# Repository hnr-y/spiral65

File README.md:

# Keyboard
 A simple 65 WKL keyboard.

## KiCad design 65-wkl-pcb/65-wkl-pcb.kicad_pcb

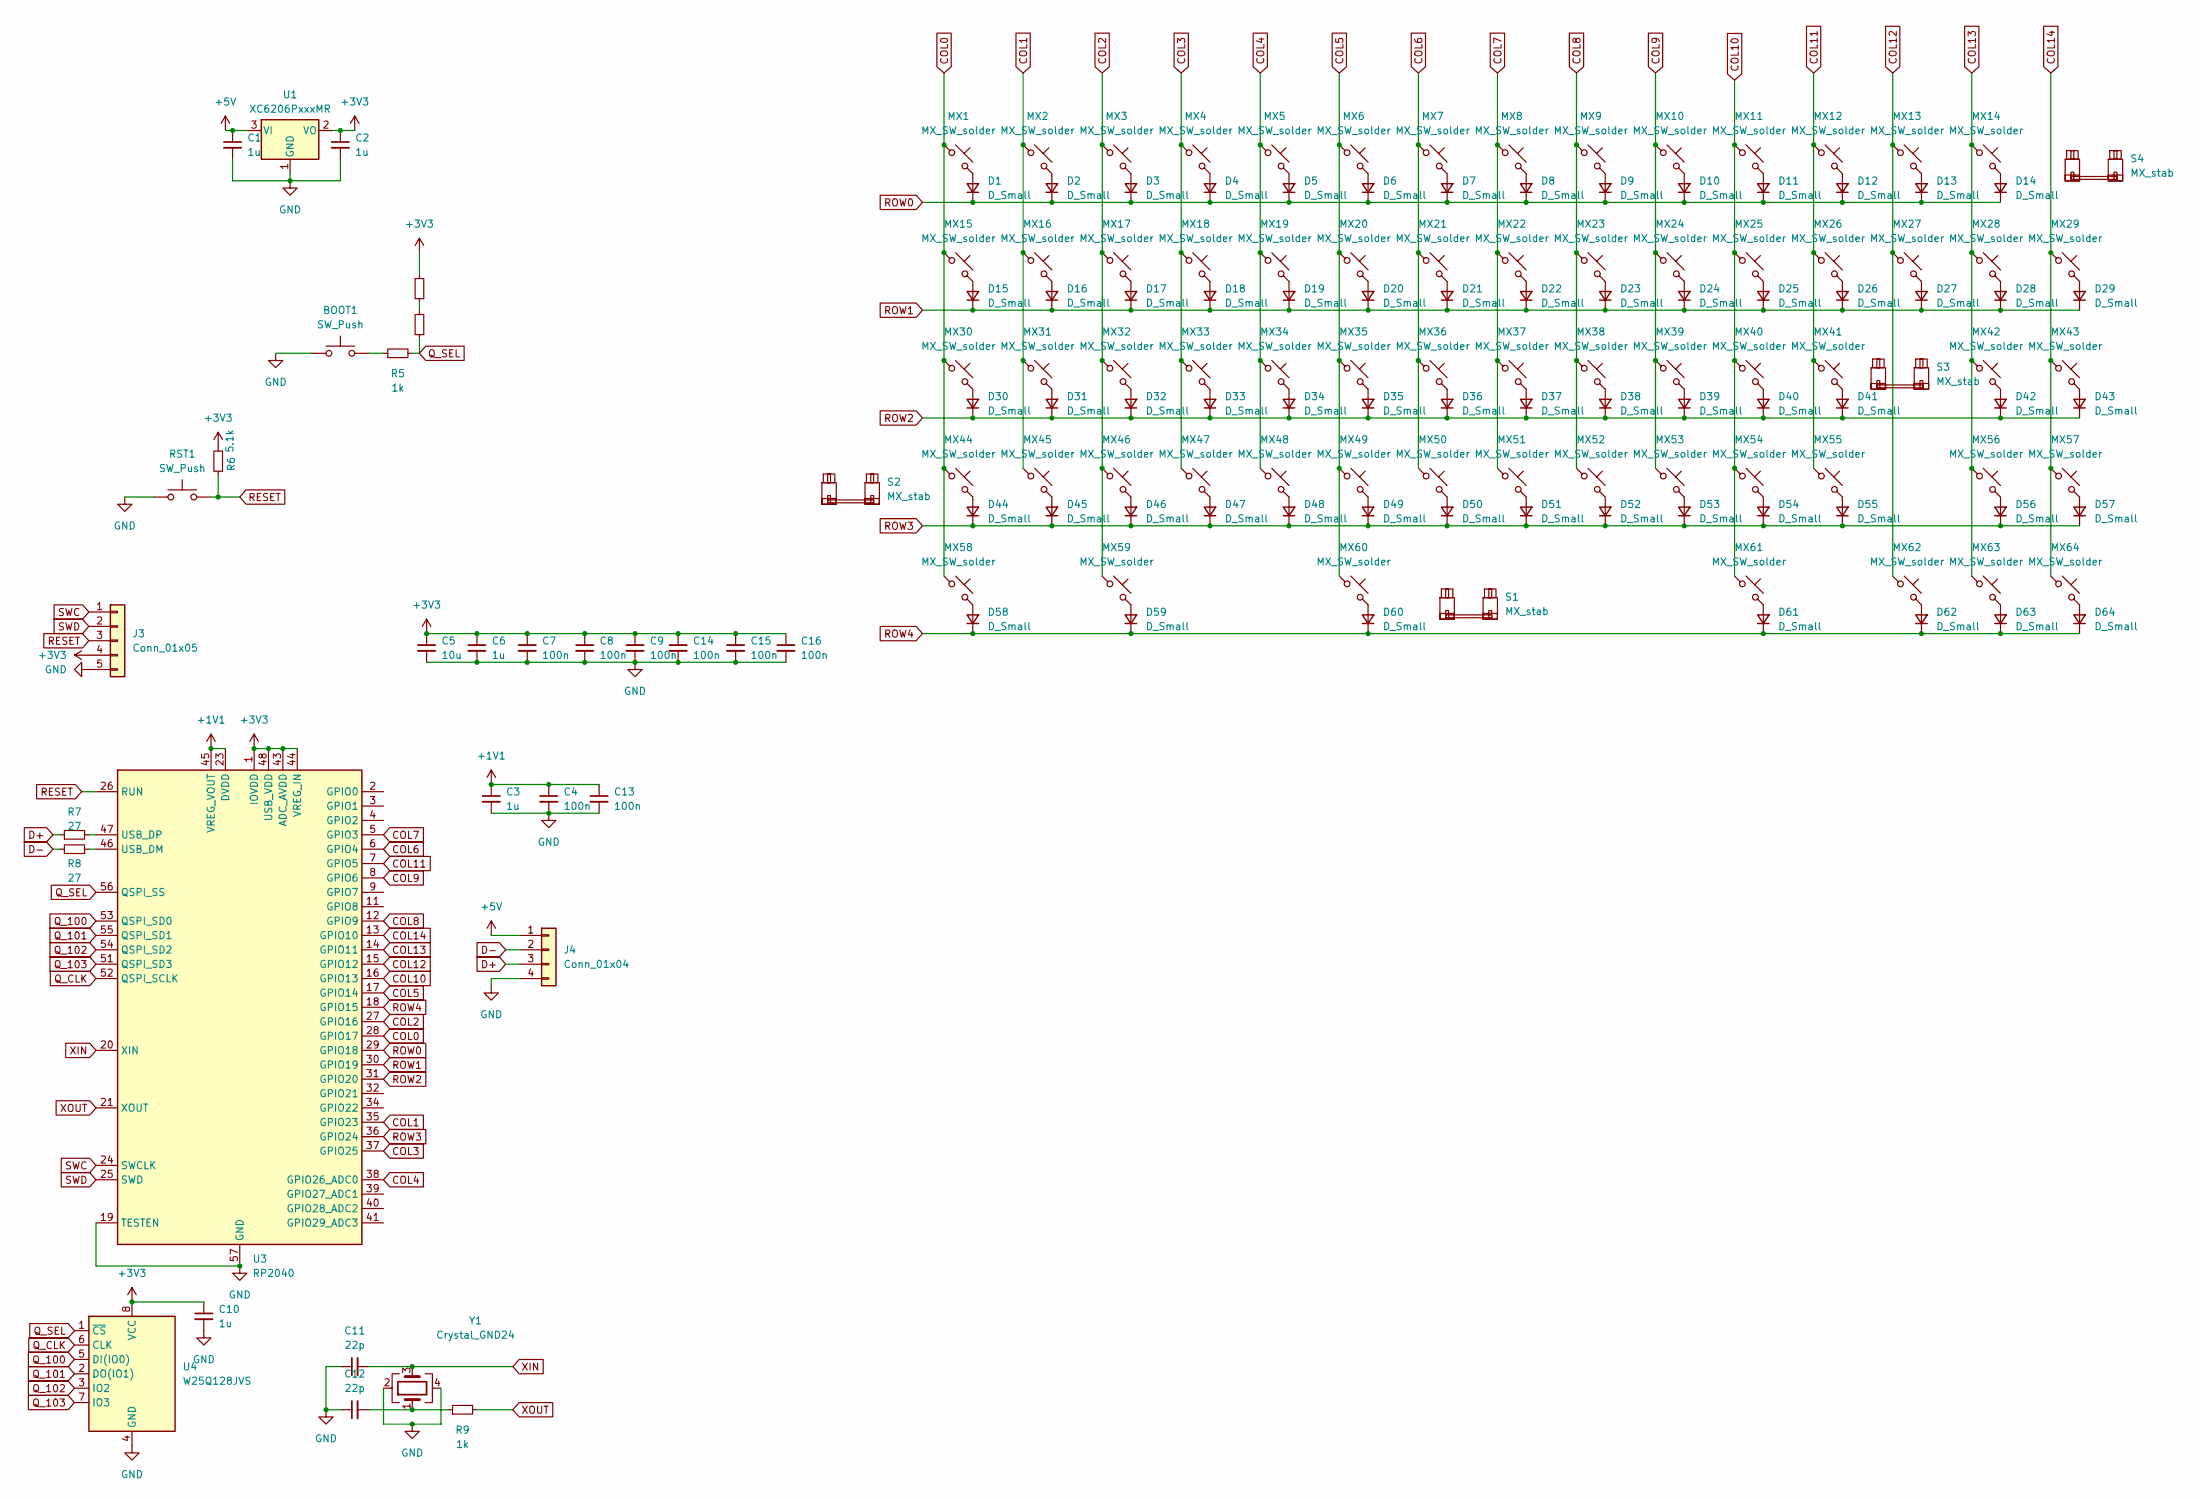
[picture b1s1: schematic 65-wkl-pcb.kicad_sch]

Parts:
BOOT1: SW_Push; SW_SPST_TL3342
C1, C2, C3, C6, C10: 1u; C_0402_1005Metric
C4, C7, C8, C9, C13, C14, C15, C16: 100n; C_0402_1005Metric
C5: 10u; C_0603_1608Metric
C11, C12: 22p; C_0402_1005Metric
D1, D2, D3, D4, D5, D6, D7, D8, D9, D10, D11, D12, D13, D14, D15, D16, D17, D18, D19, D20, D21, D22, D23, D24, D25, D26, D27, D28, D29, D30, D31, D32, D33, D34, D35, D36, D37, D38, D39, D40, D41, D42, D43, D44, D45, D46, D47, D48, D49, D50, D51, D52, D53, D54, D55, D56, D57, D58, D59, D60, D61, D62, D63, D64: D_Small; D_SOD-123
J3: Conn_01x05; PinHeader_1x05_P2.54mm_Vertical
J4: Conn_01x04; Molex_Pico-EZmate_78171-0004_1x04-1MP_P1.20mm_Vertical
MX1, MX2, MX3, MX4, MX5, MX6, MX7, MX8, MX9, MX10, MX11, MX12, MX13, MX14, MX16, MX17, MX18, MX19, MX20, MX21, MX22, MX23, MX24, MX25, MX26, MX27, MX28, MX29, MX31, MX32, MX33, MX34, MX35, MX36, MX37, MX38, MX39, MX40, MX41, MX42, MX43, MX44, MX45, MX46, MX47, MX48, MX49, MX50, MX51, MX52, MX53, MX54, MX56, MX57, MX60, MX61, MX62, MX63, MX64: MX_SW_solder; SW_MX_1u
MX15, MX58, MX59: MX_SW_solder; SW_MX_1.5u
MX30, MX55: MX_SW_solder; SW_MX_1.75u
R3, R4, R6: 5.1k; R_0402_1005Metric
R5, R9: 1k; R_0402_1005Metric
R7, R8: 27; R_0402_1005Metric
RST1: SW_Push; SW_SPST_TL3342
S1: MX_stab; STAB_MX_P_7u
S2, S3: MX_stab; STAB_MX_P_2.25u
S4: MX_stab; STAB_MX_P_2u
U1: XC6206PxxxMR; SOT-23-3
U3: RP2040; QFN-56-1EP_7x7mm_P0.4mm_EP3.2x3.2mm
U4: W25Q128JVS; SOIC-8_5.23x5.23mm_P1.27mm
Y1: Crystal_GND24; Crystal_SMD_3225-4Pin_3.2x2.5mm

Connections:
+1V1: C3.1, C4.1, C13.1, U3.23 (DVDD), U3.45 (VREG_VOUT), U3.50 (DVDD)
+3V3: C2.1, C5.1, C6.1, C7.1, C8.1, C9.1, C10.1, C14.1, C15.1, C16.1, J3.4, R3.2, R6.2, U1.2 (VO), U3.1 (IOVDD), U3.10 (IOVDD), U3.22 (IOVDD), U3.33 (IOVDD), U3.42 (IOVDD), U3.43 (ADC_AVDD), U3.44 (VREG_IN), U3.48 (USB_VDD), U3.49 (IOVDD), U4.8 (VCC)
+5V: C1.1, J4.1, U1.3 (VI)
COL0: MX1.1, MX15.1, MX30.1, MX44.1, MX58.1, U3.28 (GPIO17)
COL1: MX2.1, MX16.1, MX31.1, MX45.1, U3.35 (GPIO23)
COL2: MX3.1, MX17.1, MX32.1, MX46.1, MX59.1, U3.27 (GPIO16)
COL3: MX4.1, MX18.1, MX33.1, MX47.1, U3.37 (GPIO25)
COL4: MX5.1, MX19.1, MX34.1, MX48.1, U3.38 (GPIO26_ADC0)
COL5: MX6.1, MX20.1, MX35.1, MX49.1, MX60.1, U3.17 (GPIO14)
COL6: MX7.1, MX21.1, MX36.1, MX50.1, U3.6 (GPIO4)
COL7: MX8.1, MX22.1, MX37.1, MX51.1, U3.5 (GPIO3)
COL8: MX9.1, MX23.1, MX38.1, MX52.1, U3.12 (GPIO9)
COL9: MX10.1, MX24.1, MX39.1, MX53.1, U3.8 (GPIO6)
COL10: MX11.1, MX25.1, MX40.1, MX54.1, MX61.1, U3.16 (GPIO13)
COL11: MX12.1, MX26.1, MX41.1, MX55.1, U3.7 (GPIO5)
COL12: MX13.1, MX27.1, MX62.1, U3.15 (GPIO12)
COL13: MX14.1, MX28.1, MX42.1, MX56.1, MX63.1, U3.14 (GPIO11)
COL14: MX29.1, MX43.1, MX57.1, MX64.1, U3.13 (GPIO10)
D+: J4.3, R7.1
D-: J4.2, R8.1
GND: BOOT1.1, C1.2, C2.2, C3.2, C4.2, C5.2, C6.2, C7.2, C8.2, C9.2, C10.2, C11.1, C12.1, C13.2, C14.2, C15.2, C16.2, J3.5, J4.4, RST1.1, U1.1 (GND), U3.19 (TESTEN), U3.57 (GND), U4.4 (GND), Y1.2, Y1.4
unnamed: BOOT1.2, R5.1
unnamed: C12.2, R9.1, Y1.1
unnamed: D1.2 (A), MX1.2
unnamed: D2.2 (A), MX2.2
unnamed: D3.2 (A), MX3.2
unnamed: D4.2 (A), MX4.2
unnamed: D5.2 (A), MX5.2
unnamed: D6.2 (A), MX6.2
unnamed: D7.2 (A), MX7.2
unnamed: D8.2 (A), MX8.2
unnamed: D9.2 (A), MX9.2
unnamed: D10.2 (A), MX10.2
unnamed: D11.2 (A), MX11.2
unnamed: D12.2 (A), MX12.2
unnamed: D13.2 (A), MX13.2
unnamed: D14.2 (A), MX14.2
unnamed: D15.2 (A), MX15.2
unnamed: D16.2 (A), MX16.2
unnamed: D17.2 (A), MX17.2
unnamed: D18.2 (A), MX18.2
unnamed: D19.2 (A), MX19.2
unnamed: D20.2 (A), MX20.2
unnamed: D21.2 (A), MX21.2
unnamed: D22.2 (A), MX22.2
unnamed: D23.2 (A), MX23.2
unnamed: D24.2 (A), MX24.2
unnamed: D25.2 (A), MX25.2
unnamed: D26.2 (A), MX26.2
unnamed: D27.2 (A), MX27.2
unnamed: D28.2 (A), MX28.2
unnamed: D29.2 (A), MX29.2
unnamed: D30.2 (A), MX30.2
unnamed: D31.2 (A), MX31.2
unnamed: D32.2 (A), MX32.2
unnamed: D33.2 (A), MX33.2
unnamed: D34.2 (A), MX34.2
unnamed: D35.2 (A), MX35.2
unnamed: D36.2 (A), MX36.2
unnamed: D37.2 (A), MX37.2
unnamed: D38.2 (A), MX38.2
unnamed: D39.2 (A), MX39.2
unnamed: D40.2 (A), MX40.2
unnamed: D41.2 (A), MX41.2
unnamed: D42.2 (A), MX42.2
unnamed: D43.2 (A), MX43.2
unnamed: D44.2 (A), MX44.2
unnamed: D45.2 (A), MX45.2
unnamed: D46.2 (A), MX46.2
unnamed: D47.2 (A), MX47.2
unnamed: D48.2 (A), MX48.2
unnamed: D49.2 (A), MX49.2
unnamed: D50.2 (A), MX50.2
unnamed: D51.2 (A), MX51.2
unnamed: D52.2 (A), MX52.2
unnamed: D53.2 (A), MX53.2
unnamed: D54.2 (A), MX54.2
unnamed: D55.2 (A), MX55.2
unnamed: D56.2 (A), MX56.2
unnamed: D57.2 (A), MX57.2
unnamed: D58.2 (A), MX58.2
unnamed: D59.2 (A), MX59.2
unnamed: D60.2 (A), MX60.2
unnamed: D61.2 (A), MX61.2
unnamed: D62.2 (A), MX62.2
unnamed: D63.2 (A), MX63.2
unnamed: D64.2 (A), MX64.2
unnamed: R3.1, R4.2
unnamed: R8.2, U3.46 (USB_DM)
unnamed: R7.2, U3.47 (USB_DP)
Q_100: U3.53 (QSPI_SD0), U4.5 (DI(IO0))
Q_101: U3.55 (QSPI_SD1), U4.2 (DO(IO1))
Q_102: U3.54 (QSPI_SD2), U4.3 (IO2)
Q_103: U3.51 (QSPI_SD3), U4.7 (IO3)
Q_CLK: U3.52 (QSPI_SCLK), U4.6 (CLK)
Q_SEL: R4.1, R5.2, U3.56 (QSPI_SS), U4.1 (~CS)
RESET: J3.3, R6.1, RST1.2, U3.26 (RUN)
ROW0: D1.1 (K), D2.1 (K), D3.1 (K), D4.1 (K), D5.1 (K), D6.1 (K), D7.1 (K), D8.1 (K), D9.1 (K), D10.1 (K), D11.1 (K), D12.1 (K), D13.1 (K), D14.1 (K), U3.29 (GPIO18)
ROW1: D15.1 (K), D16.1 (K), D17.1 (K), D18.1 (K), D19.1 (K), D20.1 (K), D21.1 (K), D22.1 (K), D23.1 (K), D24.1 (K), D25.1 (K), D26.1 (K), D27.1 (K), D28.1 (K), D29.1 (K), U3.30 (GPIO19)
ROW2: D30.1 (K), D31.1 (K), D32.1 (K), D33.1 (K), D34.1 (K), D35.1 (K), D36.1 (K), D37.1 (K), D38.1 (K), D39.1 (K), D40.1 (K), D41.1 (K), D42.1 (K), D43.1 (K), U3.31 (GPIO20)
ROW3: D44.1 (K), D45.1 (K), D46.1 (K), D47.1 (K), D48.1 (K), D49.1 (K), D50.1 (K), D51.1 (K), D52.1 (K), D53.1 (K), D54.1 (K), D55.1 (K), D56.1 (K), D57.1 (K), U3.36 (GPIO24)
ROW4: D58.1 (K), D59.1 (K), D60.1 (K), D61.1 (K), D62.1 (K), D63.1 (K), D64.1 (K), U3.18 (GPIO15)
SWC: J3.1, U3.24 (SWCLK)
SWD: J3.2, U3.25 (SWD)
XIN: C11.2, U3.20 (XIN), Y1.3
XOUT: R9.2, U3.21 (XOUT)

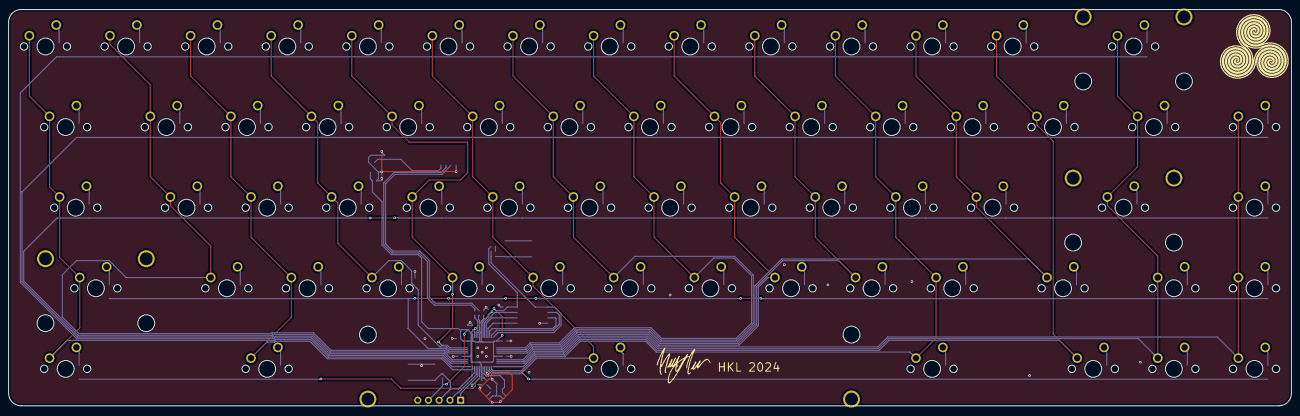
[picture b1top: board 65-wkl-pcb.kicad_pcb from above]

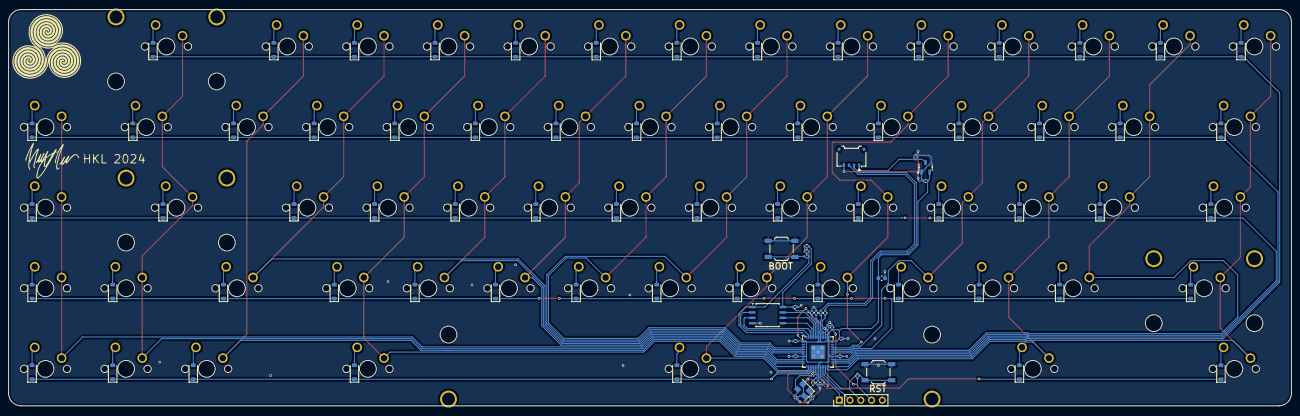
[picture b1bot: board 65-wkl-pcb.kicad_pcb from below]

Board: 2 copper layers, 303.2 x 93.7 mm, 163 parts (95 on the bottom side), 106 nets.

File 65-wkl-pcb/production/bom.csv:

Designator,Footprint,Quantity,Value,LCSC Part #
"BOOT1, RST1",SW_SPST_TL3342,2,SW_Push,
"C1, C10, C2, C3, C6",0402,5,1u,
"C11, C12",0402,2,22p,
"C13, C14, C15, C16, C4, C7, C8, C9",0402,8,100n,
C5,0603,1,10u,
"D1, D10, D11, D12, D13, D14, D15, D16, D17, D18, D19, D2, D20, D21, D22, D23, D24, D25, D26, D27, D28, D29, D3, D30, D31, D32, D33, D34, D35, D36, D37, D38, D39, D4, D40, D41, D42, D43, D44, D45, D46, D47, D48, D49, D5, D50, D51, D52, D53, D54, D55, D56, D57, D58, D59, D6, D60, D61, D62, D63, D64, D7, D8, D9",D_SOD-123,64,D_Small,
J3,PinHeader_1x05_P2.54mm_Vertical,1,Conn_01x05,
J4,Molex_Pico-EZmate_78171-0004_1x04-1MP_P1.20mm_Vertical,1,Conn_01x04,
"MX1, MX10, MX11, MX12, MX13, MX14, MX16, MX17, MX18, MX19, MX2, MX20, MX21, MX22, MX23, MX24, MX25, MX26, MX27, MX28, MX29, MX3, MX31, MX32, MX33, MX34, MX35, MX36, MX37, MX38, MX39, MX4, MX40, MX41, MX42, MX43, MX44, MX45, MX46, MX47, MX48, MX49, MX5, MX50, MX51, MX52, MX53, MX54, MX56, MX57, MX6, MX60, MX62, MX63, MX64, MX7, MX8, MX9",SW_MX_1u,58,MX_SW_solder,
"MX15, MX58, MX59, MX61",SW_MX_1.5u,4,MX_SW_solder,
"MX30, MX55",SW_MX_1.75u,2,MX_SW_solder,
"R3, R4, R6",0402,3,5.1k,
"R5, R9",0402,2,1k,
"R7, R8",0402,2,27,
S1,STAB_MX_P_7u,1,MX_stab,
"S2, S3",STAB_MX_P_2.25u,2,MX_stab,
S4,STAB_MX_P_2u,1,MX_stab,
U1,SOT-23-3,1,XC6206PxxxMR,
U3,QFN-56-1EP_7x7mm_P0.4mm_EP3.2x3.2mm,1,RP2040,
U4,SOIC-8_5.23x5.23mm_P1.27mm,1,W25Q128JVS,
Y1,Crystal_SMD_3225-4Pin_3.2x2.5mm,1,Crystal_GND24,

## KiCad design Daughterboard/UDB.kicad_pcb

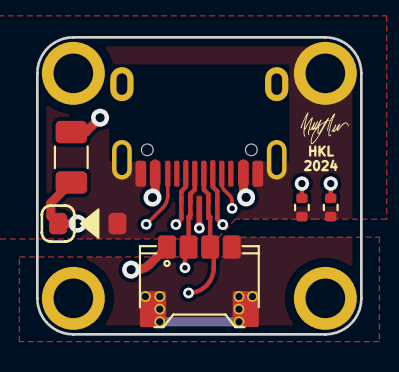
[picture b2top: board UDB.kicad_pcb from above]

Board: 4 copper layers, 18.0 x 16.5 mm, 11 parts (0 on the bottom side), 7 nets.

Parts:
D1: SMF6.0A; D_SOD-123
F1: ASMD1206-150; Fuse_1206_3216Metric
J1: TYPE-C-31-M12_13; TYPE-C-31-M-12
J2: X1224WRS-04-LPV01; PicoEZMate-Reinforced-Alt
MH1, MH2, MH3, MH4: Mount-M2; Generic-Mounthole
R1, R2: 5.1k; R_0402_1005Metric
U1: TPD4E05U06DQAR; USON-10_2.5x1.0mm_P0.5mm

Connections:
DN: J1.A7 (D-), J1.B7 (D-), J2.2, U1.2 (IO2), U1.5 (D2-), U1.6 (NC), U1.9 (NC)
DP: J1.A6 (D+), J1.B6 (D+), J2.3, U1.1 (IO1), U1.4 (D2+), U1.7 (NC), U1.10 (NC)
GND: D1.2 (A), J1.A1 (GND), J1.B1 (GND), J1.S (SHIELD), J2.4, J2.MP (MountPin), MH2.1, R1.2, R2.2, U1.3 (GND), U1.8 (GND)
unnamed: J1.A5 (CC1), R1.1
unnamed: J1.B5 (CC2), R2.1
VBUS: F1.1, J1.A4 (VBUS), J1.B4 (VBUS)
VCOM: D1.1 (K), F1.2, J2.1

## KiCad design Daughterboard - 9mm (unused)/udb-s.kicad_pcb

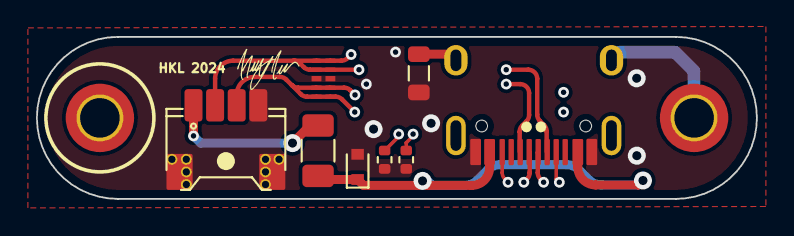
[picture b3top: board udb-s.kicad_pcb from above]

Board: 4 copper layers, 40.0 x 9.0 mm, 10 parts (0 on the bottom side), 8 nets.

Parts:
D1: ESD5Z5V0; D_SOD-523
F1: SMD0805-050-16V; Fuse_1206_3216Metric
FB1: GZ2012D601TF; L_0805_2012Metric
H1: MountingHole; MountingHole_2.2mm_M2_DIN965_Pad_TopBottom
H2: MountingHole; MountingHole_2.2mm_M2_DIN965_Pad_TopOnly
J1: TYPE-C-31-M-12; HRO-TYPE-C-31-M-12-Assembly
J2: 78171-0004; PicoEZMate-Reinforced-Lite
R1, R2: 5.1k; R_0402_1005Metric
U1: TPD4E05U06DQAR; USON-10_2.5x1.0mm_P0.5mm

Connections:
5V: F1.2, J2.1
D+: J1.A6 (D+), J1.B6 (D+), J2.3, U1.4 (D2+), U1.5 (D2-), U1.6 (NC), U1.7 (NC)
D-: J1.A7 (D-), J1.B7 (D-), J2.2, U1.1 (IO1), U1.2 (IO2), U1.9 (NC), U1.10 (NC)
GND: D1.2 (A2), FB1.2, J1.A1 (GND), J1.B1 (GND), J2.4, J2.MP (MountPin), R1.1, R2.2, U1.3 (GND), U1.8 (GND)
GNDPWR: FB1.1, H1.1, J1.S1 (SHIELD)
unnamed: J1.A5 (CC1), R1.2
unnamed: J1.B5 (CC2), R2.1
VBUS: D1.1 (A1), F1.1, J1.A4 (VBUS), J1.B4 (VBUS)

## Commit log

2024-08-23 Add pcb
2024-08-23 daughterboard production
2024-08-24 production
2024-08-24 remove daughterboard
2024-09-10 layout
